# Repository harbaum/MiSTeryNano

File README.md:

# MiSTeryNano

The MiSTeryNano is a port of the
[MiSTery Atari STE FPGA core](https://github.com/gyurco/MiSTery) to the
[Tang series of FPGA boards](https://wiki.sipeed.com/hardware/en/tang/index.html)
like the [Tang Nano 20k FPGA board](https://wiki.sipeed.com/nano20k). Recently support
for the [Efinix T20](https://www.efinixinc.com/shop/t20.php) has been added.

MiSTeryNano implements the hardware of an [Atari ST](https://de.wikipedia.org/wiki/Atari_ST) allowing it to
run the original operating systems as well as the majority of games and
productivity software of the [Atari ST](https://de.wikipedia.org/wiki/Atari_ST).

A complete MiSTeryNano setup also requires a supporting MCU acting as
the [FPGA Companion](https://github.com/harbaum/FPGA-Companion/).

For support and more information please visit the [Atari forum](https://www.atari-forum.com/viewtopic.php?p=457209).

## Current state

The MiSTeryNano's current features are:

  * Atari ST/STE
    * Complete Atari ST/E chipset
    * ST or STE configurable
    * Cycle exact 8 MHz 68000 CPU
    * 4MB RAM, optional 8MB STRAM
    * color and monochrome video via HDMI
    * YM2149 and STE DMA sound via HDMI
    * Blitter
  * Supports most TOS versions
  * Full IKBD implementation
    * Mapped to USB via [FPGA Companion](https://github.com/harbaum/FPGA-Companion/)
    * Mouse and keyboard via USB
    * Joystick via USB or dedicated IO pins of Tang Nano 20k
  * Floppy disk images
    * Read and write support for drive A: and drive B:
    * Images stored in .ST format on regular FAT/exFAT formatted SD card
  * ACSI harddisks
    * Read and write support for ACSI 0 and 1
    * Tested with AHDI, PP's driver and HDDriver 12.03
    * Images stored in .HD format
  * MIDI
    * Physical MIDI-IN and OUT
  * Optional custom carrier board like the [MiSTeryShield20k](board/misteryshield20k/) or [MiSTeryShield20k RPiPico](https://github.com/vossstef/tang_nano_20k_c64/tree/main/board/misteryshield20k_rpipico)
  * [Optional case](https://github.com/prcoder-1/MiSTeryNano-Case)
  * Runs on various Tang variants
    * [Tang Nano 20k](https://wiki.sipeed.com/nano20k)
    * [Tang Primer 25k](TANG_PRIMER_25K.md)
    * [Tang Mega 138k](TANG_MEGA_138K.md)
    * [Tang Console 60k](TANG_CONSOLE_60K.md)	
    * [Efinix T20BGA256](src/efinix/t20_bga256/README.md)
  * Supports different MCUs for the [FPGA Companion](https://github.com/harbaum/FPGA-Companion/)
    * [TN20K / TC60k onboard BL616](https://github.com/harbaum/FPGA-Companion/tree/main/src/bl616)
    * [M0S Dock/BL616](https://github.com/harbaum/FPGA-Companion/tree/main/src/bl616)
    * [Raspberry Pi Pico/RP2040](https://github.com/harbaum/FPGA-Companion/tree/main/src/rp2040)
    * [ESP32-S2 and S3](https://github.com/harbaum/FPGA-Companion/tree/main/src/esp32)

## Videos

These videos primarily document the progress during development:
  * [MiSTeryNano #23: Going online as if it's 1990](https://www.youtube.com/shorts/LzfyftSwXaw)
  * [MiSTeryNano #22: Running Atari ST demo on Efinix Trion T20 FPGA](https://youtube.com/shorts/_95nhmBHSxg)
  * [MiSTeryNano #21: I built a half sized keyboard for my FPGA Atari ST](https://youtube.com/shorts/clQujxjdr9I)

<details><summary>More ...</summary>
<ul>
  <li><a href="https://youtube.com/shorts/i-hUT1_UNOY">MiSTeryNano #20: Atari STE on Tang Primer 25k FPGA</a></li>
  <li><a href="https://youtube.com/shorts/CI1L_LBodlw">MiSTeryNano #19: Atari STE Stardust on Tang Mega 138K FPGA</a></li>
  <li><a href="https://youtube.com/shorts/_D7Gc8IL2GA">MiSTeryNano #18: Cheap RGB LCD for Atari ST in FPGA
  <li><a href="https://youtube.com/shorts/qh_TCCgo1xY">MiSTeryNano #17: C64 on Tang Nano 20K</a></li>
  <li><a href="https://youtube.com/shorts/IOfeoJvnrmE">MiSTeryNano #16: Atari ST MIDI Space Quest 3 on Roland MT32</a></li>
  <li><a href="https://youtube.com/shorts/-kPpSlpkzvA">MiSTeryNano #15: Power Without the Price: The Tang Nano 20k is the cheapest Atari ST</a></li>
  <li><a href="https://youtube.com/shorts/w8RZCzeMpiw">MiSTeryNano #14: Cubase MIDI audio replay with Atari ST FPGA and SAM2695</a></li>
  <li><a href="https://youtube.com/shorts/o6ABtje7zZ8">MiSTeryNano #13: Atari ST in Tang Nano 20k FPGA running Cubase 3 from Harddisk image</a></li>
  <li><a href="https://youtube.com/shorts/UPiLkYA_o0o">MiSTeryNano #12: Atari ST first boot from virtual hard disk</a></li>
  <li><a href="https://youtube.com/shorts/NP1EnRj4Fk0">MiSTeryNano #11: Advanced SD card for FPGA Atari ST</a></li>
  <li><a href="https://youtube.com/shorts/zsHYcolqtpc">MiSTeryNano #10: New OSD for the FPGA Atari ST</a></li>
  <li><a href="https://youtube.com/shorts/bP5gK3nmv-o">MiSTeryNano #9: Tang Nano 20k as USB host</a></li>
  <li><a href="https://youtube.com/shorts/jjps1x1NjhE">MiSTeryNano #8: Atari ST with USB keyboard and touchpad</a></li>
  <li><a href="https://youtube.com/shorts/Ud1P1vE5j84">MiSTeryNano #7: Tang Nano 20k running Atari ST Oxyd2</a></li>
  <li><a href="https://youtube.com/shorts/EXPfdhlpuFI">MiSTeryNano #6: B.I.G. DEMO</a></li>
  <li><a href="https://youtube.com/shorts/xJHF-LlaHFo">MiSTeryNano #5: Playing Atari ST Frontier</a></li>
  <li><a href="https://youtube.com/shorts/FfL01D0Zg0o">MiSTeryNano #4: Drives and Blitter</a></li>
  <li><a href="https://youtube.com/shorts/9wFxQvKtOY8">MiSTeryNano #3: We got a rainbow!</a></li>
  <li><a href="https://youtube.com/shorts/yLxXRR_04UE">MiSTeryNano #2: Booting TOS 1.04 for the first time</a></li>
  <li><a href="https://youtube.com/shorts/qndojsbH9jw">MiSTeryNano #1: Is the Tang Nano 20k the cheapest and smallest Atari ST?</a></li>
</ul>
</details>

## Getting started

In order to use the MiSTeryNano the following things are needed:

  * Tang FPGA board like e.g. the [Tang Nano 20k](https://wiki.sipeed.com/nano20k) to run the MiSTeryNano core itself
  * MCU board like the [M0S Dock](https://wiki.sipeed.com/hardware/en/maixzero/m0s/m0s.html) to run the [FPGA Companion](https://github.com/harbaum/FPGA-Companion/) to connect USB keyboard and mouse
  * Breadboard to wire everything up and some jumper wires, or
  * [a MiSTeryShield](board/misteryshield20k/)
  * a USB-C to USB-A adapter to connect regular USB devices to the M0S Dock

Many other variants can be built using various Tang FPGA boards and different MCUs. 

## Installation on e.g. Tang Nano 20k

The installation of MiSTeryNano on the Tang Nano 20k using can be done
using a [Linux PC](INSTALLATION_LINUX.md) or a [Windows PC](INSTALLATION_WINDOWS.md).

See the [trouble shooting guide](TROUBLESHOOTING.md) if you run into problems.

## Wiring

The properly flashed Tang Nano 20K will boot into the Atari ST desktop
even without anything else connected. But in order to use the system
you need at least a keyboard and most likely also a mouse. These are
usually connected through the M0S Dock.

Additional connections exist for a physical DB9 joystick or
Atari ST mouse and MIDI IN and OUT. The usage of these pins
is optional. They can just be left unconnected. A joystick may
then be connected via USB instead.

## Usage

The MiSTeryNano is mainly controlled through an on-screen-display (OSD)
overlaying the main Atari ST screen. The OSD is opened using the F12
key. It can then be used to select floppy and harddisk images and to
configure the running system.

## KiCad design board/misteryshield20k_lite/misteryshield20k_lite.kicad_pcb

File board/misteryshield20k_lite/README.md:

# Minimalistic MiSTeryNano Shield for Tang Nano 20k

This is a minimalistic base board for the Tang Nano 20K.
It features:

  * Headers to plug the Tang Nano 20K
  * Integrated RP2040 intended to run the [FPGA Compantion firmware](https://github.com/harbaum/FPGA-Companion).
  * A USB-A host port
  * A USB-C port for flashing and/or power supply

PCBA production files for JLCPCB are availble [here](jlcpcb).

The board design was in inspired and is partly based on
[this RP2040 design guide](https://github.com/calliah333/RP2040-designguide).

## Flashing the FPGA Companion firmware

The RP2040 comes unprogrammed and the board will show up as a flash
drive to be programmed.  A slightly customized firmware is needed
since this board does not allow to detect the presence (or absence in
this case) of the WiFi module. Furthermore, the oscillator used needs
some slight firmware adjustment to make the board reliably.

The necessary firmware changes can be [enabled using a build option](https://github.com/harbaum/FPGA-Companion/tree/main/src/rp2040#using-the-misteryshield20k-lite). After
flashing this firmware the green LED next to the USB-C connector
should start flashing.

The board contains a BOOT button for later flashing just like any
other Raspberry Pi Pico.

## Power options

The setup can either be powered from the shields own USB-C connector
or from the USB-C connector of the Tang Nano 20k. This gives some
flexibility when using HDMI adaptors or USB hubs plugged directly into
the Tang Nano 20K or the shields USB-A port.

[PDF](schematic.pdf)

## Optional components

The board has footprints for three unpopulated 0805 LEDs with related
560 ohms resistors on the PCBs bottom. These can be populated and will
indicate the presence of USB mouse, keyboard and joystick.

Finally, a unpopulated 5 pin connector carries the SWD signals as well
the the UART RX/TX signals and can be populated for convenient
firmware development and debugging. This is designed to use a right
angle pin header mounted on the bottom side.

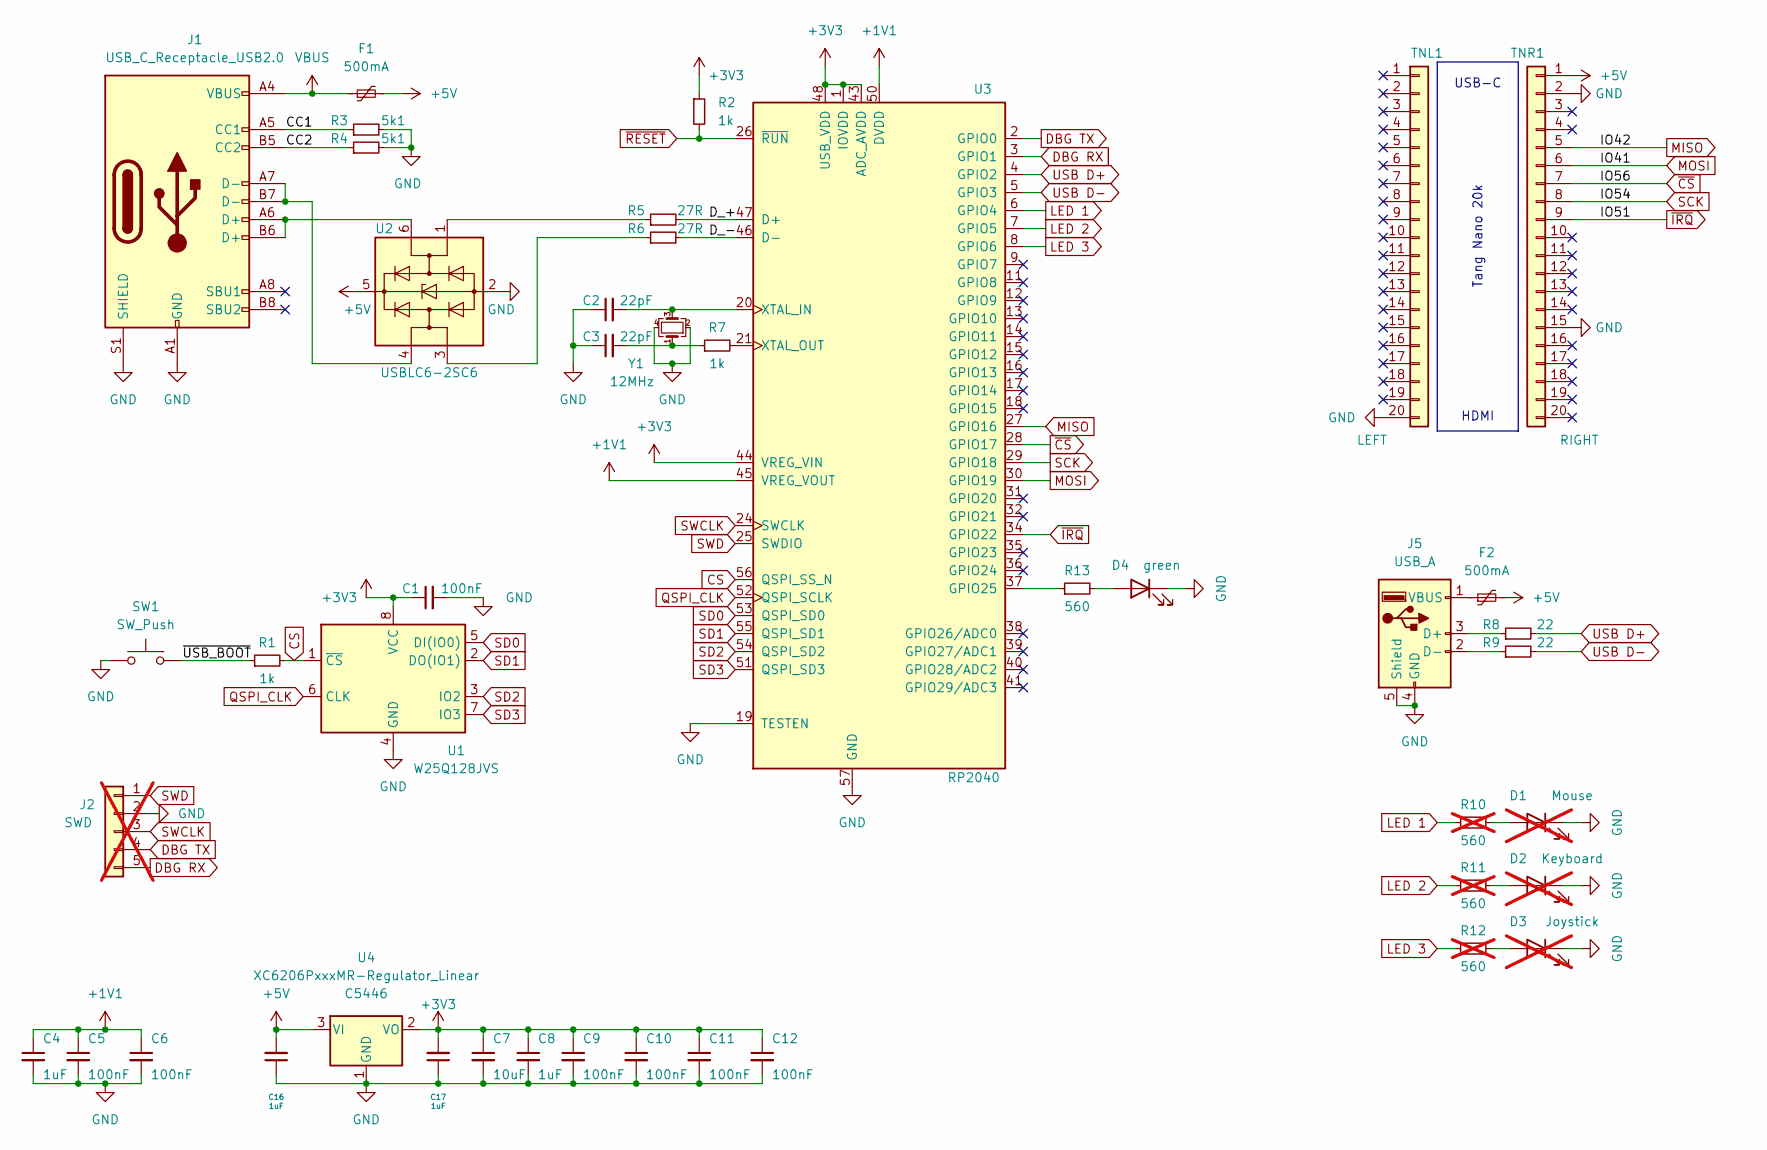
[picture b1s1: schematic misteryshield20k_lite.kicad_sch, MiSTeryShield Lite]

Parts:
C1, C5, C6, C9, C10, C11, C12: 100nF; C_0402_1005Metric; LCSC C1525
C2, C3: 22pF; C_0402_1005Metric; LCSC C1555
C4, C8, C16, C17: 1uF; C_0402_1005Metric; LCSC C52923
C7: 10uF; C_0402_1005Metric; LCSC C15525
D1: Mouse; LED_0805_2012Metric; LCSC C2297; not fitted
D2: Keyboard; LED_0805_2012Metric; LCSC C2297; not fitted
D3: Joystick; LED_0805_2012Metric; LCSC C2297; not fitted
D4: green; LED_0805_2012Metric; LCSC C2297
F1, F2: 500mA; Fuse_1206_3216Metric; LCSC C70076
J1: USB_C_Receptacle_USB2.0; USB_C_Receptacle_HRO_TYPE-C-31-M-12; LCSC C165948
J2: SWD; PinSocket_1x05_P2.54mm_Vertical; not fitted
J5: USB_A; USB_A_Molex_67643_Horizontal; LCSC C2346
R1, R2, R7: 1k; R_0402_1005Metric; LCSC C11702
R3, R4: 5k1; R_0402_1005Metric; LCSC C25905
R5, R6: 27R; R_0603_1608Metric; LCSC C25190
R8, R9: 22; R_0603_1608Metric; LCSC C1203
R10, R11, R12: 560; R_0805_2012Metric; not fitted
R13: 560; R_0402_1005Metric; LCSC C163460
SW1: SW_Push; SW_SPST_TL3342; LCSC C318884
TNL1: LEFT; PinSocket_1x20_P2.54mm_Vertical; LCSC C5224030
TNR1: RIGHT; PinSocket_1x20_P2.54mm_Vertical; LCSC C5224030
U1: W25Q128JVS; SOIC-8_5.23x5.23mm_P1.27mm; LCSC C131025
U2: USBLC6-2SC6; SOT-23-6; LCSC C2827654
U3: RP2040; RP2040-QFN-56; LCSC C2040
U4: XC6206PxxxMR-Regulator_Linear; SOT-23; LCSC C5446
Y1: 12MHz; Crystal_SMD_3225-4Pin_3.2x2.5mm; LCSC C9002

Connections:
+1V1: C4.1, C5.1, C6.1, U3.23 (DVDD), U3.45 (VREG_VOUT), U3.50 (DVDD)
+3V3: C1.1, C7.1, C8.1, C9.1, C10.1, C11.1, C12.1, C17.2, R2.1, U1.8 (VCC), U3.1 (IOVDD), U3.10 (IOVDD), U3.22 (IOVDD), U3.33 (IOVDD), U3.42 (IOVDD), U3.43 (ADC_AVDD), U3.44 (VREG_VIN), U3.48 (USB_VDD), U3.49 (IOVDD), U4.2 (VO)
+5V: C16.2, F1.2, F2.2, TNR1.1, U2.5 (VBUS), U4.3 (VI)
/CC1: J1.A5 (CC1), R3.1
/CC2: J1.B5 (CC2), R4.1
/D_+: R5.2, U3.47 (D+)
/D_-: R6.2, U3.46 (D-)
/~USB_BOOT: R1.1, SW1.2
CS: R1.2, U1.1 (~CS), U3.56 (QSPI_SS_N)
DBG RX: J2.5, U3.3 (GPIO1)
DBG TX: J2.4, U3.2 (GPIO0)
GND: C1.2, C2.1, C3.1, C4.2, C5.2, C6.2, C7.2, C8.2, C9.2, C10.2, C11.2, C12.2, C16.1, C17.1, D1.1 (K), D2.1 (K), D3.1 (K), D4.1 (K), J1.A1 (GND), J1.A12 (GND), J1.B1 (GND), J1.B12 (GND), J1.S1 (SHIELD), J2.2, J5.4 (GND), J5.5 (Shield), R3.2, R4.2, SW1.1, TNL1.20, TNR1.2, TNR1.15, U1.4 (GND), U2.2 (GND), U3.19 (TESTEN), U3.57 (GND), U4.1 (GND), Y1.2, Y1.4
LED 1: R10.1, U3.6 (GPIO4)
LED 2: R11.1, U3.7 (GPIO5)
LED 3: R12.1, U3.8 (GPIO6)
MISO: TNR1.5, U3.27 (GPIO16)
MOSI: TNR1.6, U3.30 (GPIO19)
unnamed: C3.2, R7.1, Y1.1
unnamed: D1.2 (A), R10.2
unnamed: D2.2 (A), R11.2
unnamed: D3.2 (A), R12.2
unnamed: D4.2 (A), R13.2
unnamed: J1.A6 (D+), J1.B6 (D+), U2.6 (I/O1)
unnamed: J1.A7 (D-), J1.B7 (D-), U2.4 (I/O2)
unnamed: J5.3 (D+), R8.1
unnamed: J5.2 (D-), R9.1
unnamed: F2.1, J5.1 (VBUS)
unnamed: R5.1, U2.1 (I/O1)
unnamed: R6.1, U2.3 (I/O2)
unnamed: R13.1, U3.37 (GPIO25)
unnamed: C2.2, U3.20 (XTAL_IN), Y1.3
unnamed: R7.2, U3.21 (XTAL_OUT)
QSPI_CLK: U1.6 (CLK), U3.52 (QSPI_SCLK)
SCK: TNR1.8, U3.29 (GPIO18)
SD0: U1.5 (DI(IO0)), U3.53 (QSPI_SD0)
SD1: U1.2 (DO(IO1)), U3.55 (QSPI_SD1)
SD2: U1.3 (IO2), U3.54 (QSPI_SD2)
SD3: U1.7 (IO3), U3.51 (QSPI_SD3)
SWCLK: J2.3, U3.24 (SWCLK)
SWD: J2.1, U3.25 (SWDIO)
USB D+: R8.2, U3.4 (GPIO2)
USB D-: R9.2, U3.5 (GPIO3)
VBUS: F1.1, J1.A4 (VBUS), J1.A9 (VBUS), J1.B4 (VBUS), J1.B9 (VBUS)
~CS: TNR1.7, U3.28 (GPIO17)
~IRQ: TNR1.9, U3.34 (GPIO22)
~RESET: R2.2, U3.26 (~RUN)

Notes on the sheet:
USB-C
Tang Nano 20k
HDMI

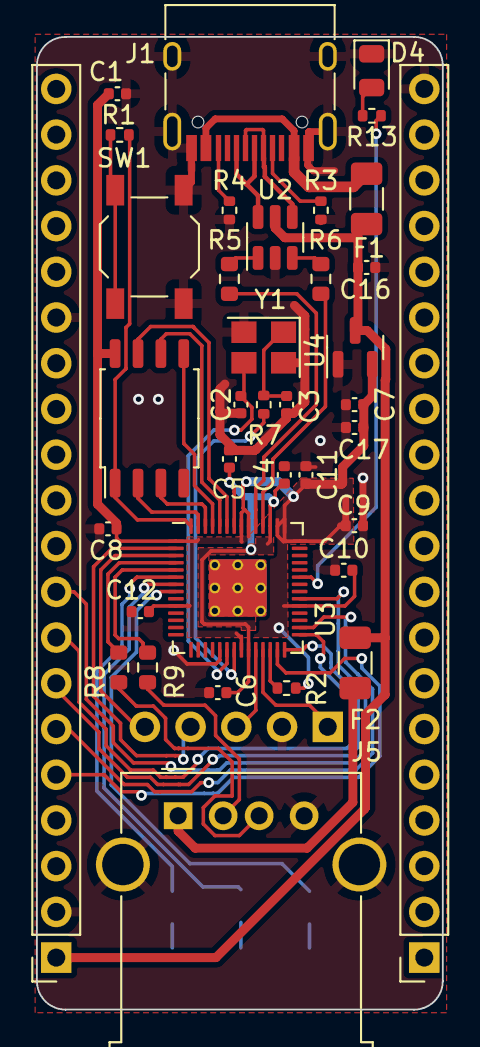
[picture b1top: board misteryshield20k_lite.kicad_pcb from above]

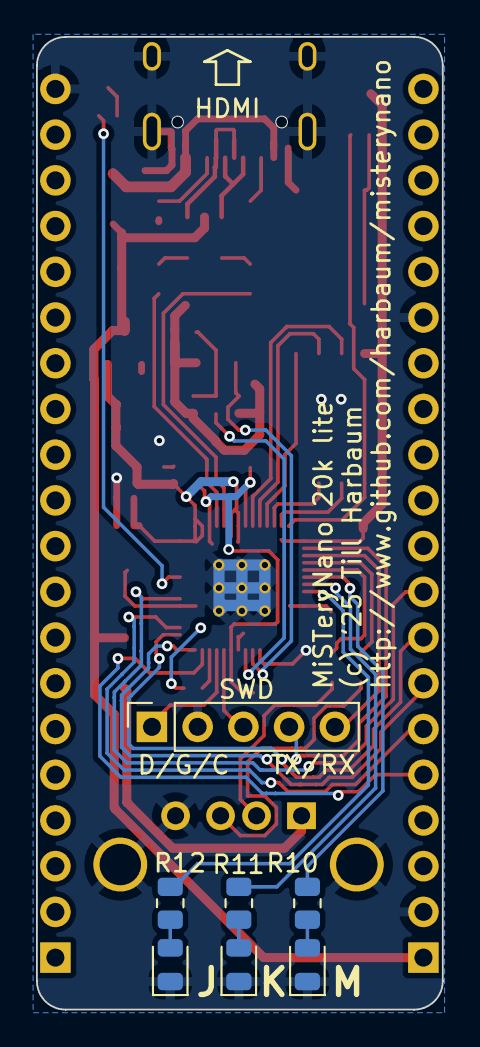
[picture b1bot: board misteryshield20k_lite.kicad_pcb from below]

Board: 2 copper layers, 22.6 x 54.0 mm, 44 parts (7 on the bottom side), 46 nets.

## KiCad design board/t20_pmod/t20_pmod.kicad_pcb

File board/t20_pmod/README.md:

# T20BGA256 MiSTeryNano PMOD

This is an add-on for the [Efinix T20BGA256 development board](https://www.efinixinc.com/products-devkits-triont20.html). It adds all components needed for a complete MiSTeryNano setup.

  * SD card slot
  * PMOD connector for use with HDMI PMOD
  * Raspberry Pi PICO
  * USB-A host connector

The board plugs into the ```Bank 1B_1C``` header.

## Components

The following additional items are required:

  * [```Sipeed DVI PMOD```](https://wiki.sipeed.com/hardware/en/tang/tang-PMOD/FPGA_PMOD.html), ```iCESugar HDMi PMOD``` or similar
  * [USB-A](https://de.aliexpress.com/item/32888479323.html)
  * [SD-card breakout](https://de.aliexpress.com/item/32799352825.html)
    * 5x 22ohms 0805 resistors
    * 1x 100nF and 1x 10uF 0805 capacitor
  * 90 degree 2x06 pin 2.54mm socket (PMOD connector)
  * 1x02 and 2x18 pin 2.54 pin socket (to plug into the bank header)
  * some 2.54mm pin headers or wires

## Design files

The board was designed with KiCAD. Ready to used gerber files
are [provided as well](t20_pmod_gerbers.zip).

[PDF](t20_pmod.pdf)

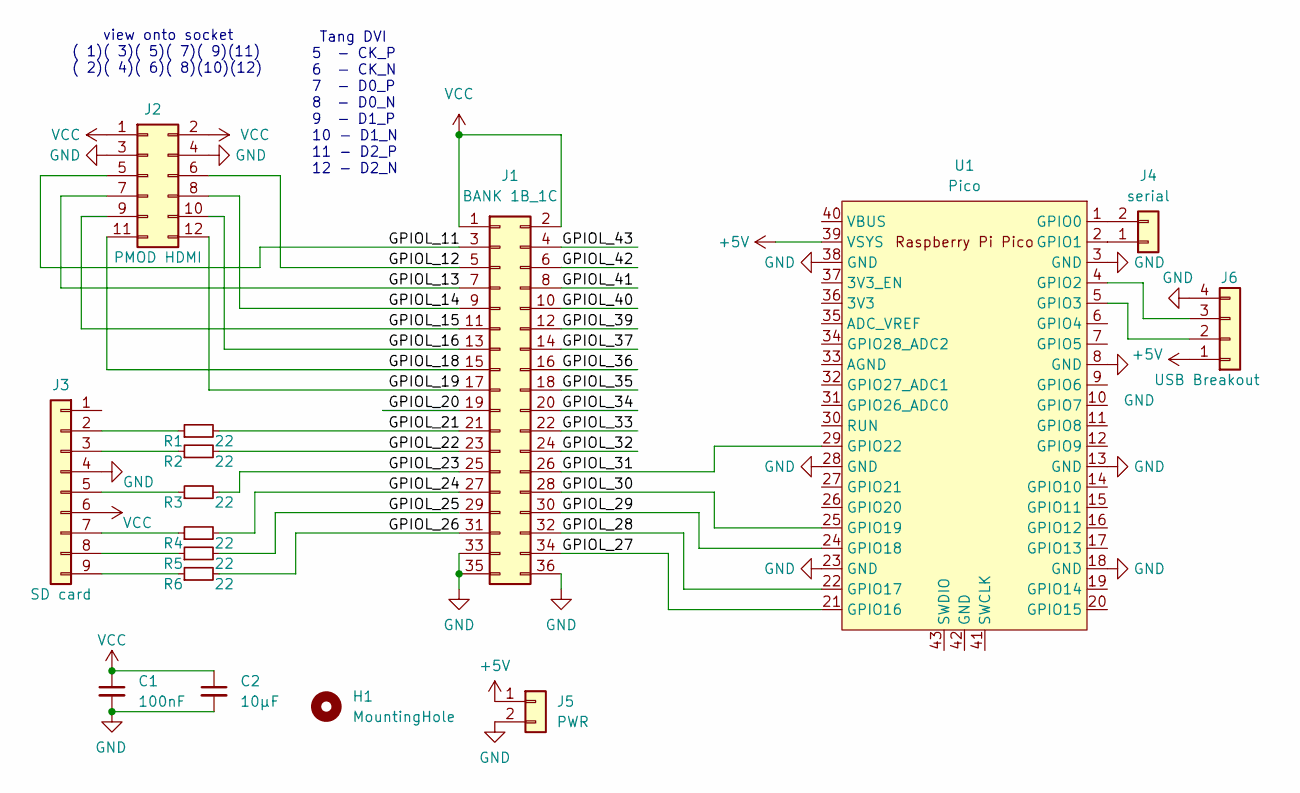
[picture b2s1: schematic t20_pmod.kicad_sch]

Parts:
C1: 100nF; C_0805_2012Metric
C2: 10µF; C_0805_2012Metric
H1: MountingHole; MountingHole_3mm
J1: BANK 1B_1C; PinSocket_2x18_P2.54mm_Vertical
J2: PMOD HDMI; PinSocket_2x06_P2.54mm_Horizontal
J3: SD card; PinHeader_1x09_P2.00mm_Vertical
J4: serial; PinHeader_1x02_P2.54mm_Vertical
J5: PWR; PinSocket_1x02_P2.54mm_Vertical
J6: USB Breakout; PinHeader_1x04_P2.54mm_Vertical
R1, R2, R3, R4, R5, R6: 22; R_0805_2012Metric
U1: Pico; RPi_Pico_SMD_TH

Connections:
+5V: J5.1, J6.1, U1.39 (VSYS)
/GPIOL_11: J1.3, J2.5
/GPIOL_12: J1.5, J2.6
/GPIOL_13: J1.7, J2.7
/GPIOL_14: J1.9, J2.8
/GPIOL_15: J1.11, J2.9
/GPIOL_16: J1.13, J2.10
/GPIOL_18: J1.15, J2.11
/GPIOL_19: J1.17, J2.12
/GPIOL_20: J1.19
/GPIOL_21: J1.21, R1.2
/GPIOL_22: J1.23, R2.2
/GPIOL_23: J1.25, R3.2
/GPIOL_24: J1.27, R4.2
/GPIOL_25: J1.29, R5.2
/GPIOL_26: J1.31, R6.2
/GPIOL_27: J1.34, U1.21 (GPIO16)
/GPIOL_28: J1.32, U1.22 (GPIO17)
/GPIOL_29: J1.30, U1.24 (GPIO18)
/GPIOL_30: J1.28, U1.25 (GPIO19)
/GPIOL_31: J1.26, U1.29 (GPIO22)
/GPIOL_32: J1.24
/GPIOL_33: J1.22
/GPIOL_34: J1.20
/GPIOL_35: J1.18
/GPIOL_36: J1.16
/GPIOL_37: J1.14
/GPIOL_39: J1.12
/GPIOL_40: J1.10
/GPIOL_41: J1.8
/GPIOL_42: J1.6
/GPIOL_43: J1.4
GND: C1.2, C2.2, J1.33, J1.35, J1.36, J2.3, J2.4, J3.4, J5.2, J6.4, U1.3 (GND), U1.8 (GND), U1.13 (GND), U1.18 (GND), U1.23 (GND), U1.28 (GND), U1.38 (GND)
unnamed: J3.2, R1.1
unnamed: J3.3, R2.1
unnamed: J3.5, R3.1
unnamed: J3.7, R4.1
unnamed: J3.8, R5.1
unnamed: J3.9, R6.1
unnamed: J4.1, U1.2 (GPIO1)
unnamed: J4.2, U1.1 (GPIO0)
unnamed: J6.2, U1.5 (GPIO3)
unnamed: J6.3, U1.4 (GPIO2)
VCC: C1.1, C2.1, J1.1, J1.2, J2.1, J2.2, J3.6

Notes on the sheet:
view onto socket ( 1)( 3)( 5)( 7)( 9)(11) ( 2)( 4)( 6)( 8)(10)(12)
Tang DVI 5 - CK_P 6 - CK_N 7 - D0_P 8 - D0_N 9 - D1_P 10 - D1_N 11 - D2_P 12 - D2_N

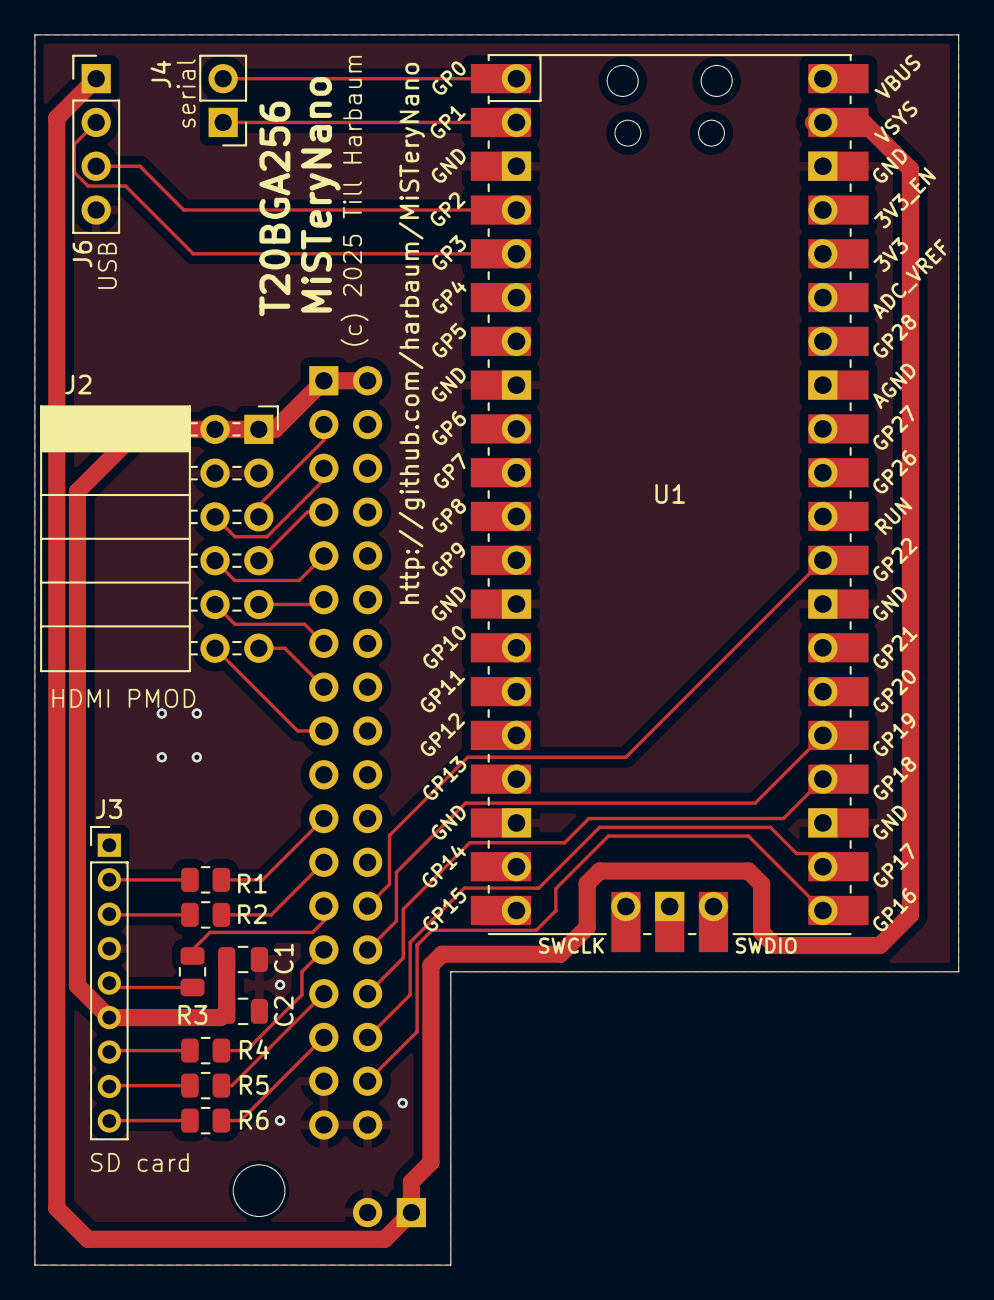
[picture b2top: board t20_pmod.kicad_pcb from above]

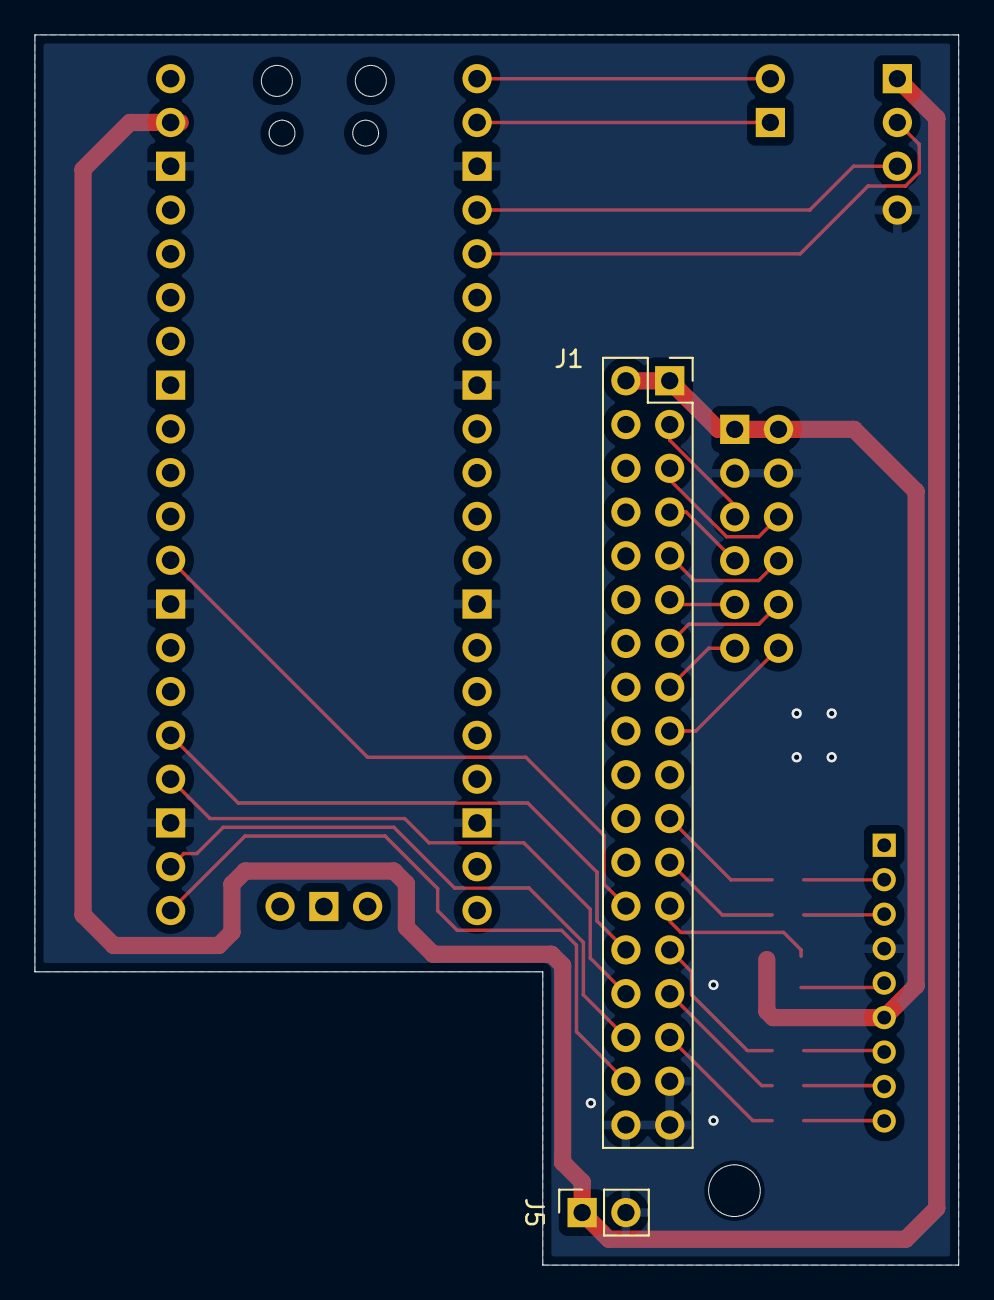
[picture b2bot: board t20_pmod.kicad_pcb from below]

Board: 2 copper layers, 53.6 x 71.4 mm, 16 parts (2 on the bottom side), 32 nets.

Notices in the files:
board/misteryshield20k/misteryshield20k_m0s.kicad_pcb:
(c) 2024 Till Harbaum
board/t20_pmod/t20_pmod.kicad_pcb:
(c) 2025 Till Harbaum
